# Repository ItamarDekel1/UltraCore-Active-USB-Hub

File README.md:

# UltraCore-Active-USB-Hub
Active USB Hub using the USB2514B From Microchip with 1 USBC upstream port, 2 USBC Downstream, and 2 USBA DownStream. Uses load switch with a stackup of sig gnd gnd sig.

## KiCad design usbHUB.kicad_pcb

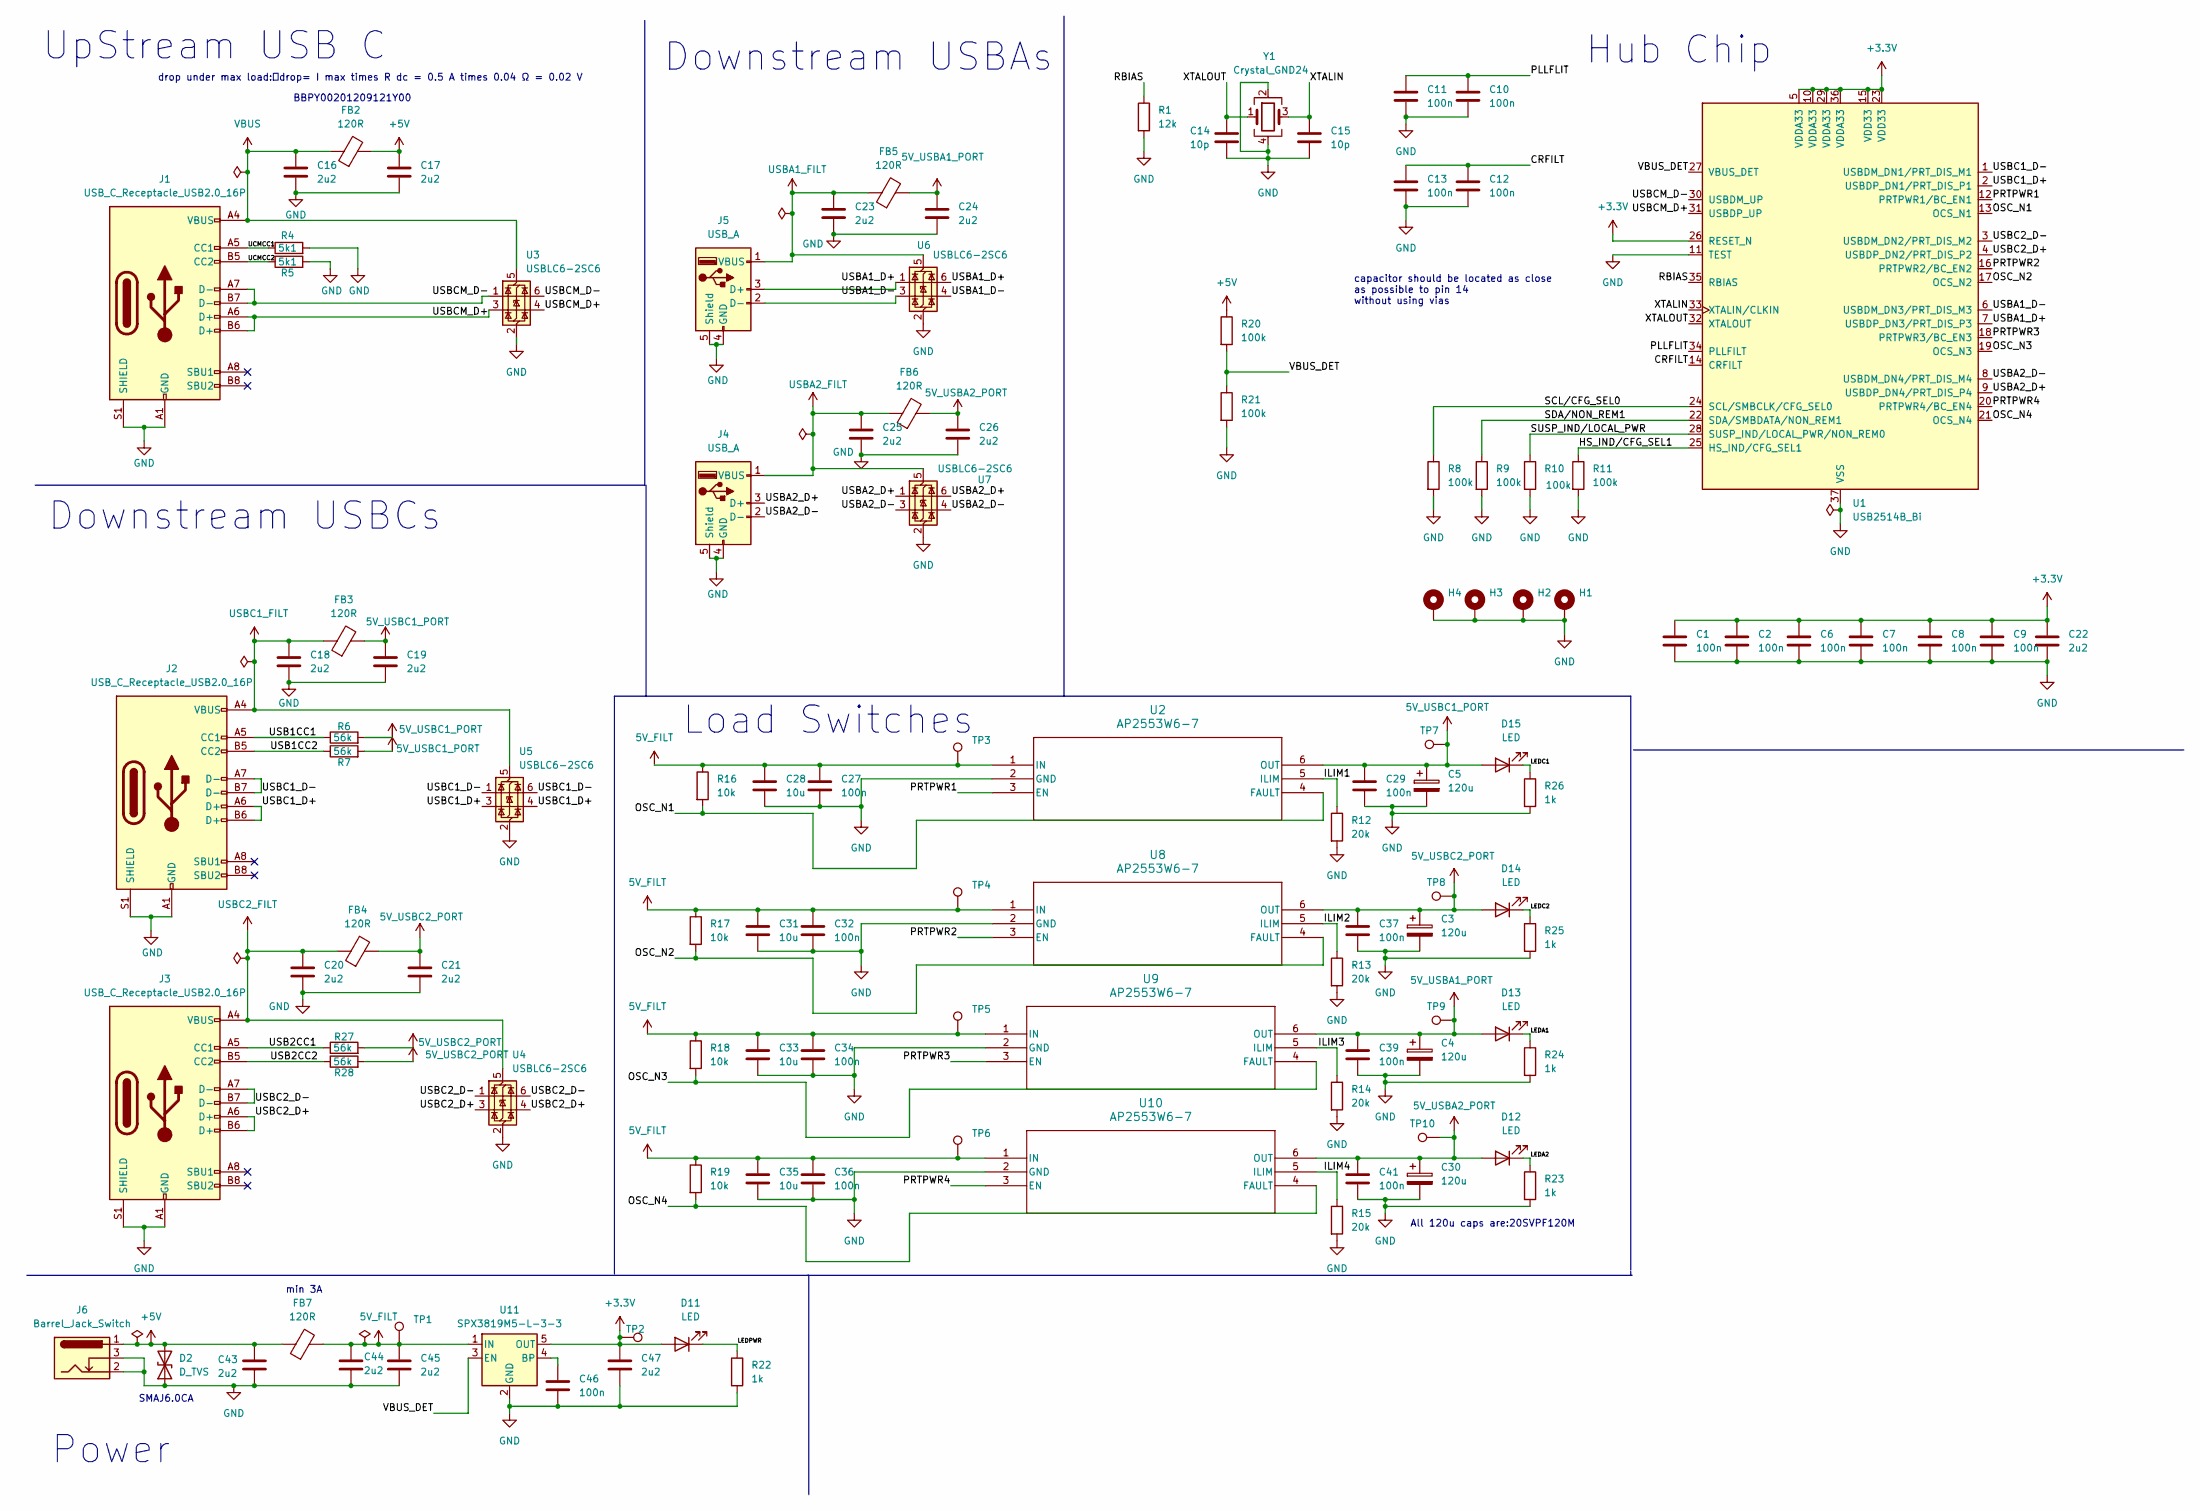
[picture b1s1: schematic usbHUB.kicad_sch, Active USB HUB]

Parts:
C1, C2, C6, C7, C8, C9, C10, C11, C12, C13, C27, C29, C32, C34, C36, C37, C39, C41, C46: 100n; C_0603_1608Metric
C3, C4, C5, C30: 120u; PCAP_SVP_C6_PAN
C14, C15: 10p; C_0402_1005Metric
C16, C17, C18, C19, C20, C21, C22, C23, C24, C25, C26, C43, C44, C45, C47: 2u2; C_0603_1608Metric
C28, C31, C33, C35: 10u; C_0402_1005Metric
D2: D_TVS; D_SMA
D11, D12, D13, D14, D15: LED; LED_0402_1005Metric
FB2, FB3, FB4, FB5, FB6, FB7: 120R; L_0805_2012Metric
H1, H2, H3, H4: MountingHole_Pad; MountingHole_2.2mm_M2_Pad_Via
J1, J2, J3: USB_C_Receptacle_USB2.0_16P; USB_C_Receptacle_GCT_USB4105-xx-A_16P_TopMnt_Horizontal
J4, J5: USB_A; OST_USB-A1HSW6
J6: Barrel_Jack_Switch; BarrelJack_Kycon_KLDX-0202-xC_Horizontal
R1: 12k; R_0402_1005Metric
R4, R5: 5k1; R_0603_1608Metric
R6, R7, R27, R28: 56k; R_0603_1608Metric
R8, R9, R10, R11, R20, R21: 100k; R_0603_1608Metric
R12, R13, R14, R15: 20k; R_0603_1608Metric
R16, R17, R18, R19: 10k; R_0402_1005Metric
R22, R23, R24, R25, R26: 1k; R_0402_1005Metric
TP1, TP2, TP3, TP4, TP5, TP6, TP7, TP8, TP9, TP10: TestPoint; TestPoint_Pad_1.5x1.5mm
U1: USB2514B_Bi; QFN-36-1EP_6x6mm_P0.5mm_EP3.7x3.7mm
U2, U8, U9, U10: AP2553W6-7; SOT95P285X140-6N
U3, U4, U5, U6, U7: USBLC6-2SC6; SOT-23-6
U11: SPX3819M5-L-3-3; SOT-23-5
Y1: Crystal_GND24; Crystal_SMD_Abracon_ABM8G-4Pin_3.2x2.5mm

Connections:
5V_FILT: C27.1, C28.1, C31.1, C32.1, C33.1, C34.1, C35.1, C36.1, C44.1, C45.1, FB7.2, R16.1, R17.1, R18.1, R19.1, TP1.1, TP3.1, TP4.1, TP5.1, TP6.1, U2.1 (IN), U8.1 (IN), U9.1 (IN), U10.1 (IN), U11.1 (IN); also elsewhere on the board
5V_USBA1_PORT: C4.1, C24.1, C39.1, D13.2 (A), FB5.2, TP9.1, U9.6 (OUT); also elsewhere on the board
5V_USBA2_PORT: C26.1, C30.1, C41.1, D12.2 (A), FB6.2, TP10.1, U10.6 (OUT); also elsewhere on the board
5V_USBC1_PORT: C5.1, C19.1, C29.1, D15.2 (A), FB3.2, R6.2, R7.2, TP7.1, U2.6 (OUT); also elsewhere on the board
5V_USBC2_PORT: C3.1, C21.1, C37.1, D14.2 (A), FB4.2, R27.2, R28.2, TP8.1, U8.6 (OUT); also elsewhere on the board
+3.3V: C1.1, C2.1, C6.1, C7.1, C8.1, C9.1, C22.1, C47.1, D11.2 (A), TP2.1, U1.5 (VDDA33), U1.10 (VDDA33), U1.15 (VDD33), U1.23 (VDD33), U1.26 (RESET_N), U1.29 (VDDA33), U1.36 (VDDA33), U11.5 (OUT)
+5V: C17.1, C43.1, D2.2 (A2), FB2.2, FB7.1, J6.1, R20.1
/CRFILT: C12.1, C13.1, U1.14 (CRFILT)
/HS_IND/CFG_SEL1: R11.1, U1.25 (HS_IND/CFG_SEL1)
/ILIM1: R12.1, U2.5 (ILIM)
/ILIM2: R13.1, U8.5 (ILIM)
/ILIM3: R14.1, U9.5 (ILIM)
/ILIM4: R15.1, U10.5 (ILIM)
/LEDA1: D13.1 (K), R24.1
/LEDA2: D12.1 (K), R23.1
/LEDC1: D15.1 (K), R26.1
/LEDC2: D14.1 (K), R25.1
/LEDPWR: D11.1 (K), R22.1
/OSC_N1: R16.2, U1.13 (OCS_N1), U2.4 (FAULT)
/OSC_N2: R17.2, U1.17 (OCS_N2), U8.4 (FAULT)
/OSC_N3: R18.2, U1.19 (OCS_N3), U9.4 (FAULT)
/OSC_N4: R19.2, U1.21 (OCS_N4), U10.4 (FAULT)
/PLLFLIT: C10.1, C11.1, U1.34 (PLLFILT)
/PRTPWR1: U1.12 (PRTPWR1/BC_EN1), U2.3 (EN)
/PRTPWR2: U1.16 (PRTPWR2/BC_EN2), U8.3 (EN)
/PRTPWR3: U1.18 (PRTPWR3/BC_EN3), U9.3 (EN)
/PRTPWR4: U1.20 (PRTPWR4/BC_EN4), U10.3 (EN)
/RBIAS: R1.1, U1.35 (RBIAS)
/SCL/CFG_SEL0: R8.1, U1.24 (SCL/SMBCLK/CFG_SEL0)
/SDA/NON_REM1: R9.1, U1.22 (SDA/SMBDATA/NON_REM1)
/SUSP_IND/LOCAL_PWR: R10.1, U1.28 (SUSP_IND/LOCAL_PWR/NON_REM0)
/UCMCC1: J1.A5 (CC1), R4.1
/UCMCC2: J1.B5 (CC2), R5.1
/USB1CC1: J2.A5 (CC1), R6.1
/USB1CC2: J2.B5 (CC2), R7.1
/USB2CC1: J3.A5 (CC1), R27.1
/USB2CC2: J3.B5 (CC2), R28.1
/USBA1_D+: J5.3 (D+), U1.7 (USBDP_DN3/PRT_DIS_P3), U6.1 (I/O1), U6.6 (I/O1)
/USBA1_D-: J5.2 (D-), U1.6 (USBDM_DN3/PRT_DIS_M3), U6.3 (I/O2), U6.4 (I/O2)
/USBA2_D+: J4.3 (D+), U1.9 (USBDP_DN4/PRT_DIS_P4), U7.1 (I/O1), U7.6 (I/O1)
/USBA2_D-: J4.2 (D-), U1.8 (USBDM_DN4/PRT_DIS_M4), U7.3 (I/O2), U7.4 (I/O2)
/USBC1_D+: J2.A6 (D+), J2.B6 (D+), U1.2 (USBDP_DN1/PRT_DIS_P1), U5.3 (I/O2), U5.4 (I/O2)
/USBC1_D-: J2.A7 (D-), J2.B7 (D-), U1.1 (USBDM_DN1/PRT_DIS_M1), U5.1 (I/O1), U5.6 (I/O1)
/USBC2_D+: J3.A6 (D+), J3.B6 (D+), U1.4 (USBDP_DN2/PRT_DIS_P2), U4.3 (I/O2), U4.4 (I/O2)
/USBC2_D-: J3.A7 (D-), J3.B7 (D-), U1.3 (USBDM_DN2/PRT_DIS_M2), U4.1 (I/O1), U4.6 (I/O1)
/USBCM_D+: J1.A6 (D+), J1.B6 (D+), U1.31 (USBDP_UP), U3.3 (I/O2), U3.4 (I/O2)
/USBCM_D-: J1.A7 (D-), J1.B7 (D-), U1.30 (USBDM_UP), U3.1 (I/O1), U3.6 (I/O1)
/VBUS_DET: R20.2, R21.1, U1.27 (VBUS_DET), U11.3 (EN)
/XTALIN: C15.1, U1.33 (XTALIN/CLKIN), Y1.3
/XTALOUT: C14.1, U1.32 (XTALOUT), Y1.1
GND: C1.2, C2.2, C3.2, C4.2, C5.2, C6.2, C7.2, C8.2, C9.2, C10.2, C11.2, C12.2, C13.2, C14.2, C15.2, C16.2, C17.2, C18.2, C19.2, C20.2, C21.2, C22.2, C23.2, C24.2, C25.2, C26.2, C27.2, C28.2, C29.2, C30.2, C31.2, C32.2, C33.2, C34.2, C35.2, C36.2, C37.2, C39.2, C41.2, C43.2, C44.2, C45.2, C46.2, C47.2, D2.1 (A1), H1.1, H2.1, H3.1, H4.1, J1.A1 (GND), J1.A12 (GND), J1.B1 (GND), J1.B12 (GND), J1.S1 (SHIELD), J2.A1 (GND), J2.A12 (GND), J2.B1 (GND), J2.B12 (GND), J2.S1 (SHIELD), J3.A1 (GND), J3.A12 (GND), J3.B1 (GND), J3.B12 (GND), J3.S1 (SHIELD), J4.4 (GND), J4.5 (Shield), J5.4 (GND), J5.5 (Shield), J6.2, J6.3, R1.2, R4.2, R5.2, R8.2, R9.2, R10.2, R11.2, R12.2, R13.2, R14.2, R15.2, R21.2, R22.2, R23.2, R24.2, R25.2, R26.2, U1.11 (TEST), U1.37 (VSS), U2.2 (GND), U3.2 (GND), U4.2 (GND), U5.2 (GND), U6.2 (GND), U7.2 (GND), U8.2 (GND), U9.2 (GND), U10.2 (GND), U11.2 (GND), Y1.2, Y1.4
unnamed: C46.1, U11.4 (BP)
USBA1_FILT: C23.1, FB5.1, J5.1 (VBUS), U6.5 (VBUS)
USBA2_FILT: C25.1, FB6.1, J4.1 (VBUS), U7.5 (VBUS)
USBC1_FILT: C18.1, FB3.1, J2.A4 (VBUS), J2.A9 (VBUS), J2.B4 (VBUS), J2.B9 (VBUS), U5.5 (VBUS)
USBC2_FILT: C20.1, FB4.1, J3.A4 (VBUS), J3.A9 (VBUS), J3.B4 (VBUS), J3.B9 (VBUS), U4.5 (VBUS)
VBUS: C16.1, FB2.1, J1.A4 (VBUS), J1.A9 (VBUS), J1.B4 (VBUS), J1.B9 (VBUS), U3.5 (VBUS)

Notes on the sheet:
min 3A
Power
Downstream USBCs
capacitor should be located as close as possible to pin 14 without using vias
UpStream USB C
Load Switches
BBPY00201209121Y00
Hub Chip
SMAJ6.0CA
drop under max load:𝑉drop= I max times R dc = 0.5 A times 0.04 Ω = 0.02 V
All 120u caps are:20SVPF120M
Downstream USBAs

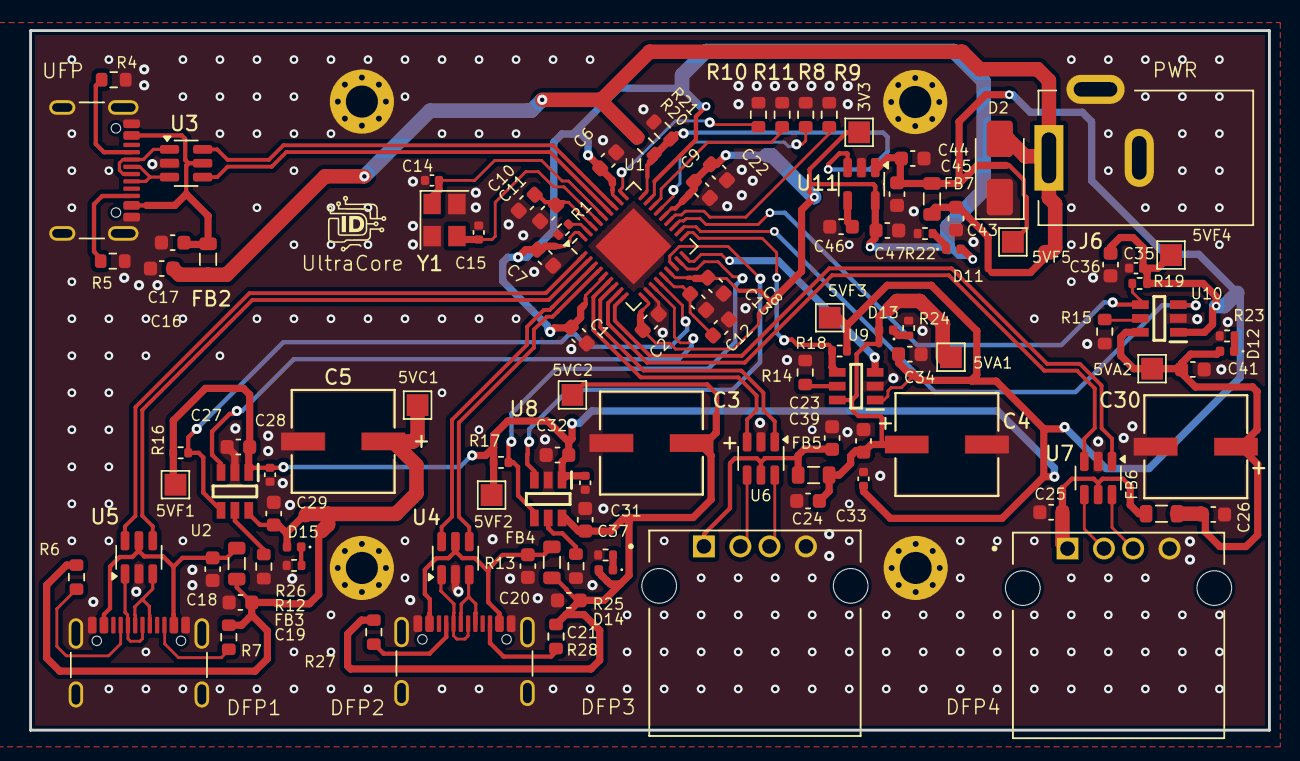
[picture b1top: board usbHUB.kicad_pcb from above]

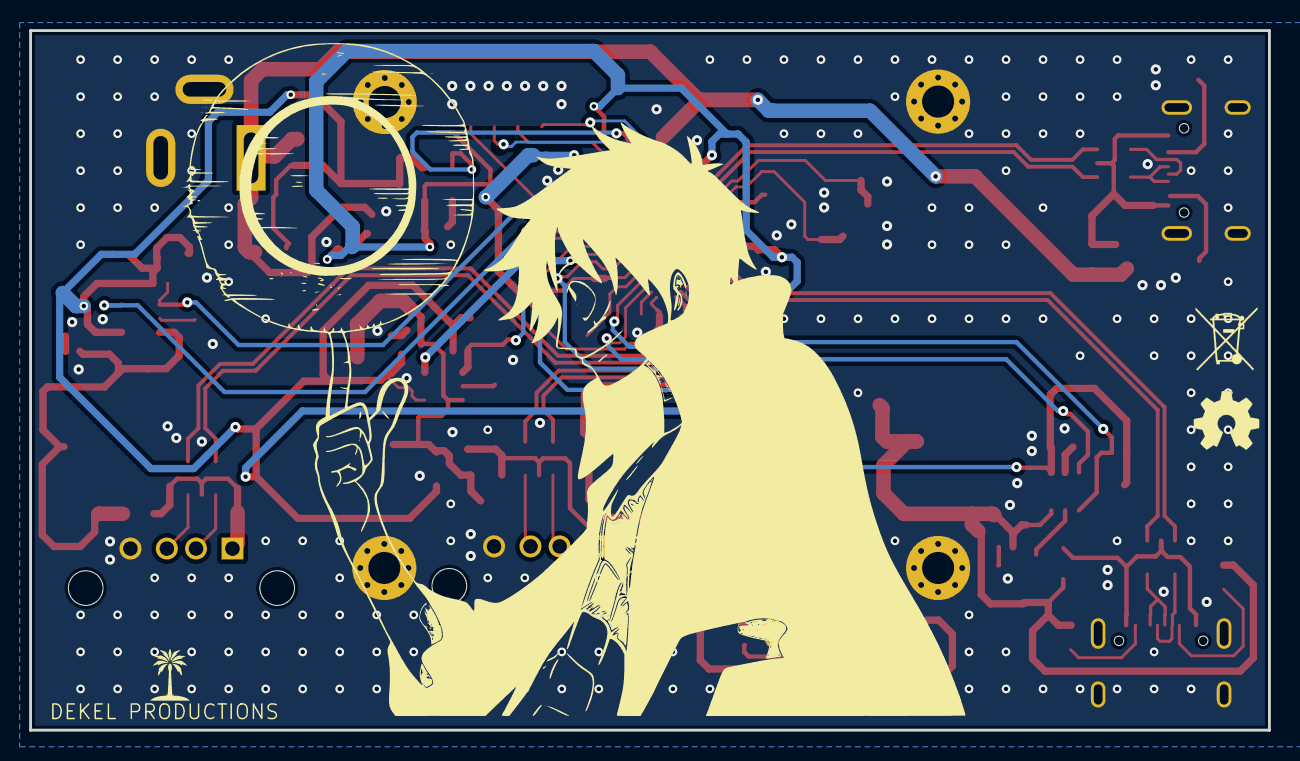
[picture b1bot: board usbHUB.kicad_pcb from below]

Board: 4 copper layers, 85.0 x 48.0 mm, 116 parts (2 on the bottom side), 57 nets.

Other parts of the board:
5VA1, 5VA2, 5VC1, 5VC2, 5VF1, 5VF2, 5VF3, 5VF4, 5VF5: TestPoint; TestPoint_Pad_1.5x1.5mm
logo1: OSHW-Logo_5.7x6mm_SilkScreen
logo2: WEEE-Logo_4.2x6mm_SilkScreen

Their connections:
5V_FILT: 5VF1.1, 5VF2.1, 5VF3.1, 5VF4.1, 5VF5.1; also elsewhere on the board
5V_USBA1_PORT: 5VA1.1; also elsewhere on the board
5V_USBA2_PORT: 5VA2.1; also elsewhere on the board
5V_USBC1_PORT: 5VC1.1; also elsewhere on the board
5V_USBC2_PORT: 5VC2.1; also elsewhere on the board
